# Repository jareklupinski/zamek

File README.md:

# Zamek
Your Digital Keychain.

I want to design the digital equivalent to the analog keychain. It keeps your passwords for you in an easy-to-use and portable, reliable design. It can be used completely standalone, but also with a Desktop App for easier data input.

Prototypes:

[Youtube Function Demo](https://www.youtube.com/watch?v=8wrW3907pkc)

Front View:

Back View:

This project is a Work-In-Progress; all contributions are welcome!

Project Layout:
* brd+sch contains hardware schematic
* desktop-app contains the desktop app
* zamek-src contains arduino source code

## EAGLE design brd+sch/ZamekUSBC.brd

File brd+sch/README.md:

Actual Schematic:

Component Layout:

Routed, produced, and smoke tested. Some validation with sensors to be done...

Front View:

Back View:

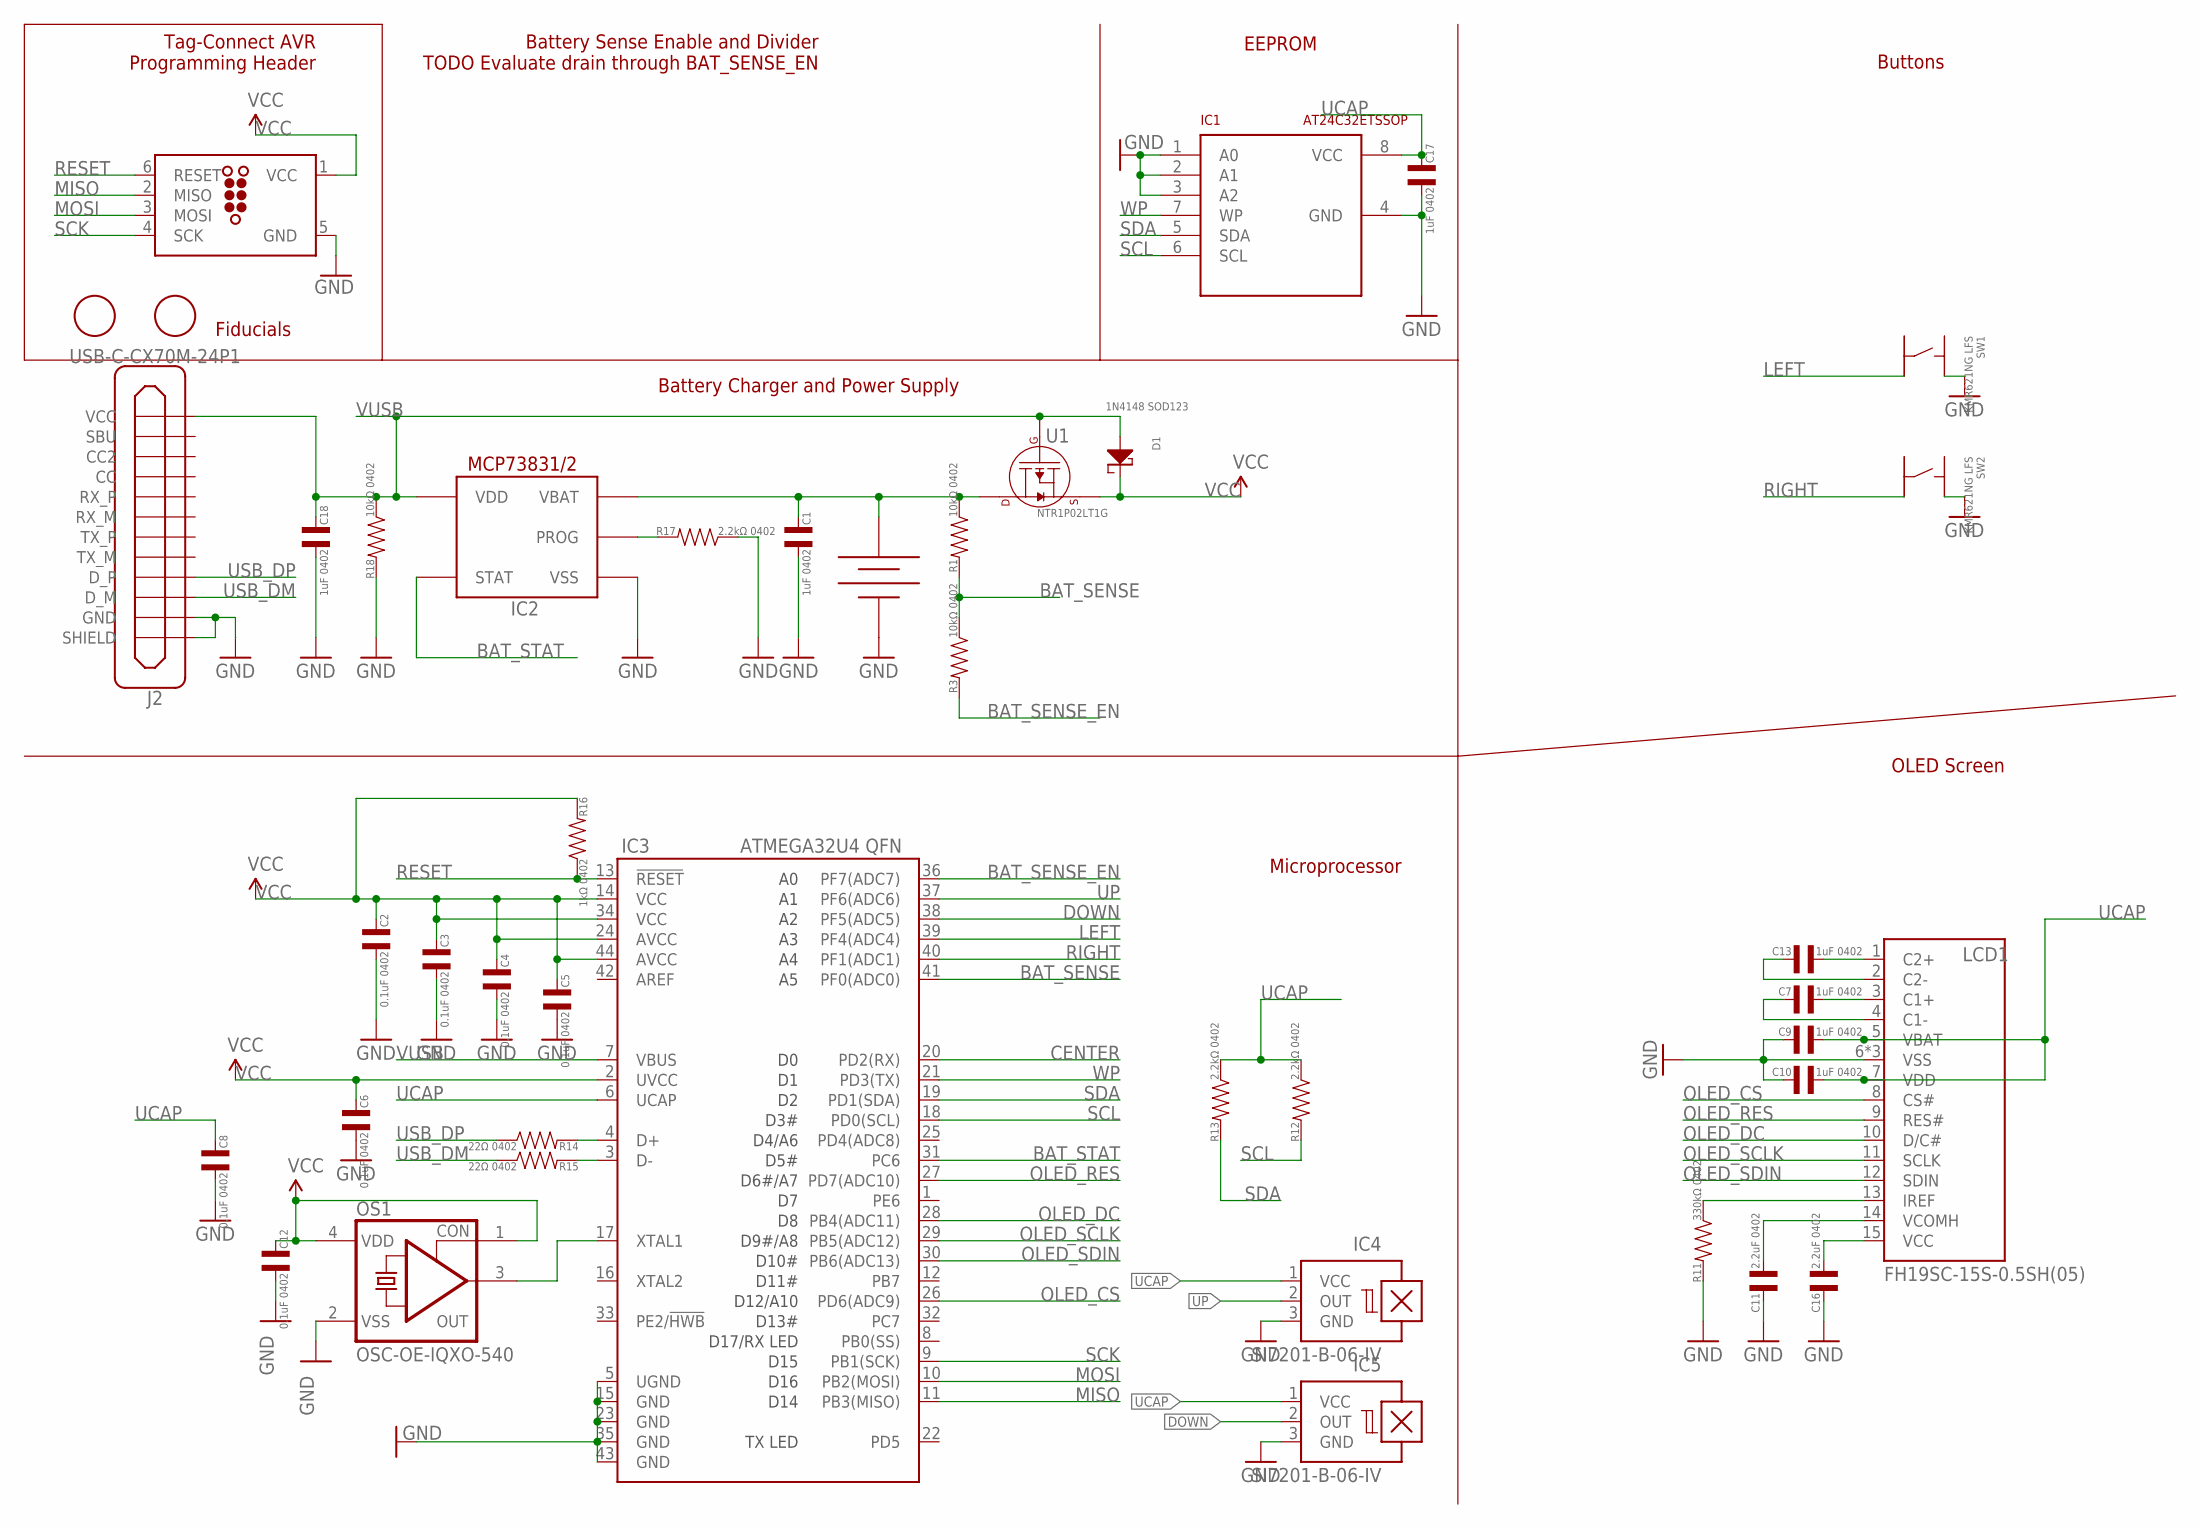
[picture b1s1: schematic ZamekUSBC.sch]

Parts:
BAT1: LIPO201030; 201030LIPO
C1, C7, C9, C10, C13, C17, C18: 1uF 0402; C0402
C2, C3, C4, C5, C6, C8, C12: 0.1uF 0402; C0402
C11, C16: 2.2uF 0402; C0402
D1: 1N4148 SOD123; SOD-123
IC1: AT24C32ETSSOP; TSSOP8-W
IC2: MCP73831; MFSOT23-5L
IC3: ATMEGA32U4 QFN; QFN-44-NOPAD
IC4, IC5: SI7201-B-06-IV; SOT23-W
J1: TC2030-MCP-NLFIX; TC2030-MCP-NL
J2: USB-C-CX70M-24P1; CX70M-24P1
LCD1: FH19SC-15S-0.5SH(05); ER-OLED0.91-3WWFH19C
OS1: OSC-OE-IQXO-540; 2.0X1.6-4-PAD
Q1, Q2: FIDUCIAL; FIDUCIAL_1MM
R1, R3, R18: 10kΩ 0402; R0402
R11: 330kΩ 0402; R0402
R12, R13, R17: 2.2kΩ 0402; R0402
R14, R15: 22Ω 0402; R0402
R16: 1kΩ 0402; R0402
SW1, SW2: KMR621NG LFS; TACT4.2MM
U1: NTR1P02LT1G; SOT-23-3

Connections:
BAT_SENSE: IC3.41 (PF0(ADC0)), R1.P$2, R3.P$1
BAT_SENSE_EN: IC3.36 (PF7(ADC7)), R3.P$2
BAT_STAT: IC2.P$1 (STAT), IC3.31 (PC6)
CENTER: IC3.20 (PD2(RX))
DOWN: IC3.38 (PF5(ADC5)), IC5.2 (OUT)
GND: BAT1.NEG, C1.P$1, C2.P$1, C3.P$1, C4.P$1, C5.P$1, C6.P$1, C8.P$1, C9.P$2, C10.P$2, C11.P$2, C12.P$1, C16.P$2, C17.P$1, C18.P$1, IC1.1 (A0), IC1.2 (A1), IC1.3 (A2), IC1.4 (GND), IC2.P$2 (VSS), IC3.5 (UGND), IC3.15 (GND), IC3.23 (GND), IC3.35 (GND), IC3.43 (GND), IC4.3 (GND), IC5.3 (GND), J1.5 (GND), J2.A1 (GND), J2.A12 (GND), J2.B1 (GND), J2.B12 (GND), J2.SHIELD@1 (SHIELD), J2.SHIELD@2 (SHIELD), J2.SHIELD@3 (SHIELD), J2.SHIELD@4 (SHIELD), LCD1.6 (VSS), LCD1.EP1 (VSS), LCD1.EP2 (VSS), OS1.2 (VSS), R11.P$2, R17.P$1, R18.P$2, SW1.P$2, SW2.P$2
LEFT: IC3.39 (PF4(ADC4)), SW1.P$4
MISO: IC3.11 (PB3(MISO)), J1.2 (MISO)
MOSI: IC3.10 (PB2(MOSI)), J1.3 (MOSI)
unnamed: C13.P$2, LCD1.2 (C2-)
unnamed: C7.P$1, LCD1.3 (C1+)
unnamed: C7.P$2, LCD1.4 (C1-)
unnamed: C13.P$1, LCD1.1 (C2+)
unnamed: IC2.P$5 (PROG), R17.P$2
unnamed: IC3.4 (D+), R14.P$2
unnamed: IC3.17 (XTAL1), OS1.3 (OUT)
unnamed: LCD1.13 (IREF), R11.P$1
unnamed: C11.P$1, LCD1.14 (VCOMH)
unnamed: IC3.3 (D-), R15.P$2
unnamed: C16.P$1, LCD1.15 (VCC)
OLED_CS: IC3.26 (PD6(ADC9)), LCD1.8 (CS#)
OLED_DC: IC3.28 (PB4(ADC11)), LCD1.10 (D/C#)
OLED_RES: IC3.27 (PD7(ADC10)), LCD1.9 (RES#)
OLED_SCLK: IC3.29 (PB5(ADC12)), LCD1.11 (SCLK)
OLED_SDIN: IC3.30 (PB6(ADC13)), LCD1.12 (SDIN)
RESET: IC3.13 (!RESET), J1.6 (RESET), R16.P$1
RIGHT: IC3.40 (PF1(ADC1)), SW2.P$4
SCK: IC3.9 (PB1(SCK)), J1.4 (SCK)
SCL: IC1.6 (SCL), IC3.18 (PD0(SCL)), R12.P$2
SDA: IC1.5 (SDA), IC3.19 (PD1(SDA)), R13.P$2
UCAP: C8.P$2, C9.P$1, C10.P$1, C17.P$2, IC1.8 (VCC), IC3.6 (UCAP), IC4.1 (VCC), IC5.1 (VCC), LCD1.5 (VBAT), LCD1.7 (VDD), R12.P$1, R13.P$1
UP: IC3.37 (PF6(ADC6)), IC4.2 (OUT)
USB_DM: J2.A7 (D_M), J2.B7 (D_M), R15.P$1
USB_DP: J2.A6 (D_P), J2.B6 (D_P), R14.P$1
VBAT: BAT1.POS, C1.P$2, IC2.P$3 (VBAT), R1.P$1, U1.P$3 (DRAIN)
VCC: C2.P$2, C3.P$2, C4.P$2, C5.P$2, C6.P$2, C12.P$2, D1.CATHODE, IC3.2 (UVCC), IC3.14 (VCC), IC3.24 (AVCC), IC3.34 (VCC), IC3.44 (AVCC), J1.1 (VCC), OS1.1 (CON), OS1.4 (VDD), R16.P$2, U1.P$2 (SOURCE)
VUSB: C18.P$2, D1.ANODE, IC2.P$4 (VDD), IC3.7 (VBUS), J2.A4 (VCC), J2.A9 (VCC), J2.B4 (VCC), J2.B9 (VCC), R18.P$1, U1.P$1 (GATE)
WP: IC1.7 (WP), IC3.21 (PD3(TX))

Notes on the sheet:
Tag-Connect AVR Programming Header
Battery Charger and Power Supply
Microprocessor
Battery Sense Enable and Divider TODO Evaluate drain through BAT_SENSE_EN
OLED Screen
Buttons
EEPROM
Fiducials

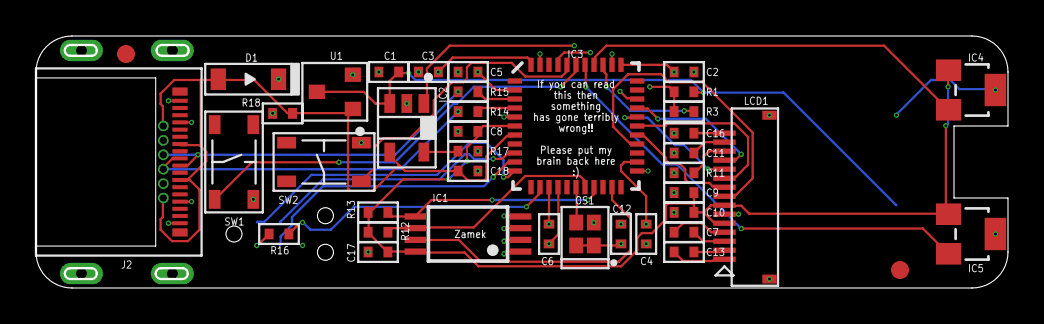
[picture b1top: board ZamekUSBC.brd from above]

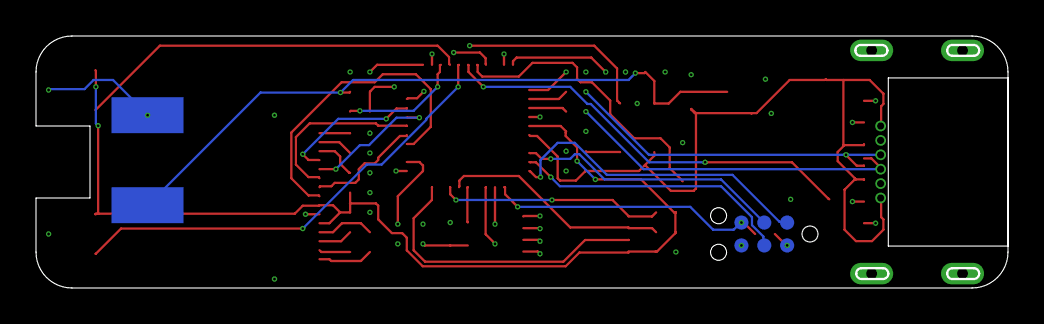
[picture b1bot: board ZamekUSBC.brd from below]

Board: 4 copper layers, 53.9 x 13.9 mm, 42 parts (2 on the bottom side), 37 nets.

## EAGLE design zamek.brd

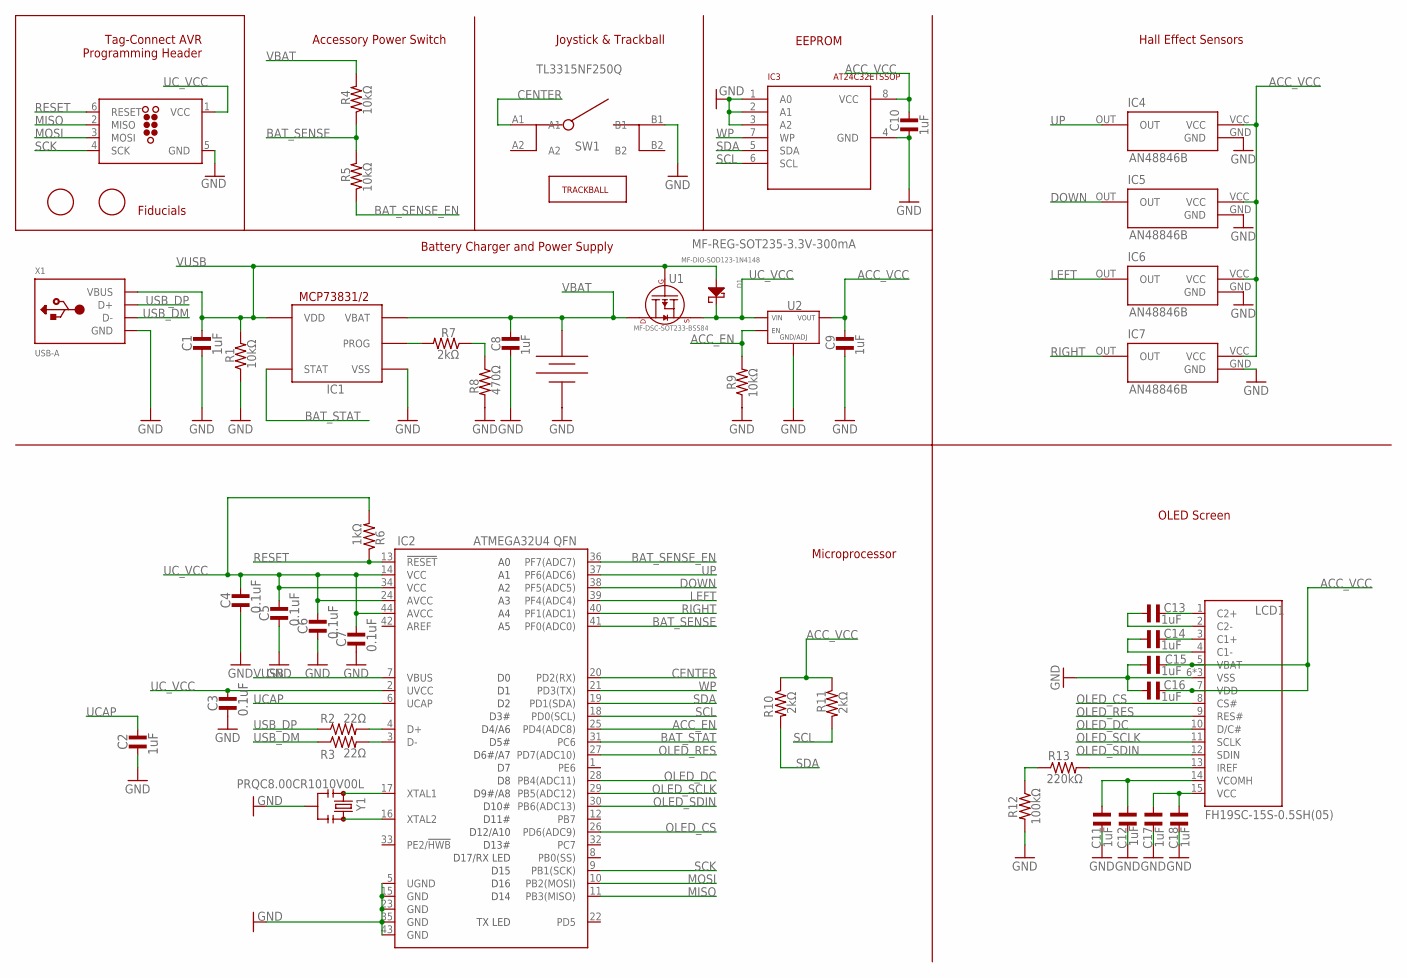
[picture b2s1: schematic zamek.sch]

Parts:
BAT1: LIPO201030; 201030LIPO
C1, C2, C8, C9, C10, C11, C12, C13, C14, C15, C16, C17, C18: 1uF; C0402
C3, C4, C5, C6, C7: 0.1uF; C0402
D1: MF-DIO-SOD123-1N4148; SOD-123
IC1: MCP73831; MFSOT23-5L
IC2: ATMEGA32U4 QFN; QFN-44-NOPAD
IC3: AT24C32ETSSOP; TSSOP8-W
IC4, IC5, IC6, IC7: AN48846B; HALLSENSOR
J1: TC2030-MCP-NLFIX; TC2030-MCP-NL
LCD1: FH19SC-15S-0.5SH(05); ER-OLED0.91-3WWFH19C
R1, R4, R5, R9: 10kΩ; R0402
R2, R3: 22Ω; R0402
R6: 1kΩ; R0402
R7, R10, R11: 2kΩ; R0402
R8: 470Ω; R0402
R12: 100kΩ; R0402
R13: 220kΩ; R0402
SW1: TL3315NF250Q; TRACKBALLBUTTON
SW2: TRACKBALLMECH; TRACKBALL
U1: MF-DSC-SOT233-BSS84; SOT-23-3
U2: MF-REG-SOT235-3.3V-300mA; SOT-23-5
U$1, U$2: FIDUCIAL; FIDUCIAL_1MM
X1: USB-A; MOLEX_480371000
Y1: PRQC8.00CR1010V00L; RESONATOR-SMD

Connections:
ACC_EN: IC2.25 (PD4(ADC8)), R9.P$2, U2.P$3 (EN)
ACC_VCC: C9.P$1, C10.P$1, C15.P$2, C16.P$1, IC3.8 (VCC), IC4.VCC, IC5.VCC, IC6.VCC, IC7.VCC, LCD1.5 (VBAT), LCD1.7 (VDD), R10.P$1, R11.P$1, U2.P$5 (VOUT)
BAT_SENSE: IC2.41 (PF0(ADC0)), R4.P$1, R5.P$2
BAT_SENSE_EN: IC2.36 (PF7(ADC7)), R5.P$1
BAT_STAT: IC1.P$1 (STAT), IC2.31 (PC6)
CENTER: IC2.20 (PD2(RX)), SW1.A1
DOWN: IC2.38 (PF5(ADC5)), IC5.OUT
GND: BAT1.NEG, C1.P$2, C2.P$2, C3.P$2, C4.P$2, C5.P$2, C6.P$2, C7.P$2, C8.P$2, C9.P$2, C10.P$2, C11.P$2, C12.P$2, C15.P$1, C16.P$2, C17.P$2, C18.P$2, IC1.P$2 (VSS), IC2.5 (UGND), IC2.15 (GND), IC2.23 (GND), IC2.35 (GND), IC2.43 (GND), IC3.1 (A0), IC3.2 (A1), IC3.3 (A2), IC3.4 (GND), IC4.GND, IC5.GND, IC6.GND, IC7.GND, J1.5 (GND), LCD1.6 (VSS), LCD1.EP1 (VSS), LCD1.EP2 (VSS), R1.P$1, R8.P$2, R9.P$1, R12.P$2, SW1.B1, U2.P$2 (GND/ADJ), U2.P$4 (GND/ADJ), X1.4 (GND), Y1.2
LEFT: IC2.39 (PF4(ADC4)), IC6.OUT
MISO: IC2.11 (PB3(MISO)), J1.2 (MISO)
MOSI: IC2.10 (PB2(MOSI)), J1.3 (MOSI)
unnamed: C13.P$1, LCD1.2 (C2-)
unnamed: C14.P$2, LCD1.3 (C1+)
unnamed: C14.P$1, LCD1.4 (C1-)
unnamed: C13.P$2, LCD1.1 (C2+)
unnamed: IC1.P$5 (PROG), R7.P$2
unnamed: R12.P$1, R13.P$1
unnamed: IC2.16 (XTAL2), Y1.3
unnamed: LCD1.13 (IREF), R13.P$2
unnamed: C11.P$1, C12.P$1, LCD1.14 (VCOMH)
unnamed: IC2.4 (D+), R2.P$2
unnamed: IC2.3 (D-), R3.P$2
unnamed: IC2.17 (XTAL1), Y1.1
unnamed: R7.P$1, R8.P$1
unnamed: C17.P$1, C18.P$1, LCD1.15 (VCC)
OLED_CS: IC2.26 (PD6(ADC9)), LCD1.8 (CS#)
OLED_DC: IC2.28 (PB4(ADC11)), LCD1.10 (D/C#)
OLED_RES: IC2.27 (PD7(ADC10)), LCD1.9 (RES#)
OLED_SCLK: IC2.29 (PB5(ADC12)), LCD1.11 (SCLK)
OLED_SDIN: IC2.30 (PB6(ADC13)), LCD1.12 (SDIN)
RESET: IC2.13 (!RESET), J1.6 (RESET), R6.P$1
RIGHT: IC2.40 (PF1(ADC1)), IC7.OUT
SCK: IC2.9 (PB1(SCK)), J1.4 (SCK)
SCL: IC2.18 (PD0(SCL)), IC3.6 (SCL), R11.P$2
SDA: IC2.19 (PD1(SDA)), IC3.5 (SDA), R10.P$2
UCAP: C2.P$1, IC2.6 (UCAP)
UC_VCC: C3.P$1, C4.P$1, C5.P$1, C6.P$1, C7.P$1, D1.CATHODE, IC2.2 (UVCC), IC2.14 (VCC), IC2.24 (AVCC), IC2.34 (VCC), IC2.44 (AVCC), J1.1 (VCC), R6.P$2, U1.P$2 (SOURCE), U2.P$1 (VIN)
UP: IC2.37 (PF6(ADC6)), IC4.OUT
USB_DM: R3.P$1, X1.2 (D-)
USB_DP: R2.P$1, X1.3 (D+)
VBAT: BAT1.POS, C8.P$1, IC1.P$3 (VBAT), R4.P$2, U1.P$3 (DRAIN)
VUSB: C1.P$1, D1.ANODE, IC1.P$4 (VDD), IC2.7 (VBUS), R1.P$2, U1.P$1 (GATE), X1.1 (VBUS)
WP: IC2.21 (PD3(TX)), IC3.7 (WP)

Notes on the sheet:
Tag-Connect AVR Programming Header
Battery Charger and Power Supply
Microprocessor
Joystick & Trackball
Accessory Power Switch
OLED Screen
Hall Effect Sensors
EEPROM
Fiducials

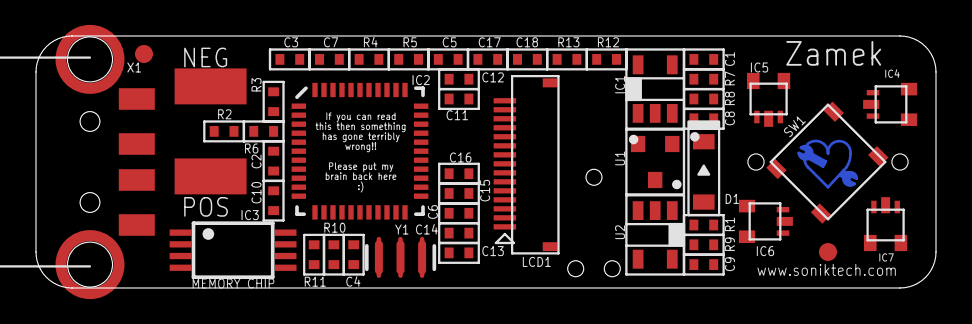
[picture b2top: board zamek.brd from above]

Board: 4 copper layers, 50.0 x 14.0 mm, 50 parts (1 on the bottom side), 43 nets.

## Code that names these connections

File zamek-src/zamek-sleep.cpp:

 #include "zamek-sleep.h"

GLOBAL_VARIABLES

void ZamekSleep::start() {               //enter Sleep Mode
  for ( int i = 0; i < 16; i++ ) pinArray[ i ] = 0;
  pinArrayIndex = 0;
  zamekDisplay.wipeScreen();
  zamekDisplay.drawBitmap( 48, 0, lock, 32, 32, WHITE );
  zamekDisplay.display();
  while ( !digitalRead( BUTTON_CENTER_PIN ));
  zamekDisplay.ssd1306_command( SSD1306_DISPLAYOFF );
  
  pinMode( BUTTON_UP_PIN     , INPUT_PULLUP );
  pinMode( BUTTON_DOWN_PIN   , INPUT_PULLUP );
  pinMode( BUTTON_LEFT_PIN   , INPUT_PULLUP );
  pinMode( BUTTON_RIGHT_PIN  , INPUT_PULLUP );
  pinMode( BAT_SENSE_PIN     , INPUT );
  pinMode( BAT_SENSE_EN_PIN  , INPUT );
  pinMode( BAT_STAT_PIN      , INPUT );
  pinMode( EEPROM_WP_PIN     , INPUT );
  // pinMode( ACC_EN_PIN        , INPUT );
  pinMode( OLED_MOSI_PIN     , INPUT );
  pinMode( OLED_CLK_PIN      , INPUT );
  pinMode( OLED_DC_PIN       , INPUT );
  pinMode( OLED_RESET_PIN    , INPUT );
  pinMode( OLED_CS_PIN       , INPUT );

  set_sleep_mode( SLEEP_MODE_PWR_DOWN ); // Set CPU Sleep Mode
  analogReference( DEFAULT ); // Power down internal reference
  PLLCSR &= ~( 1 << PLLE );   // Disable the USB Clock (PPL)
  USBCON &= ~( 1 << USBE );   // Disable the USB
  UDINT  &= ~( 1 << SUSPI );  // UDINT.SUSPI = 0; Usb_ack_suspend
  USBCON |=  ( 1 << FRZCLK ); // USBCON.FRZCLK = 1; Usb_freeze_clock
  ADCSRA = 0b00000000;        // Disable ADC
  power_adc_disable();
  wdt_disable();  
  sleep_enable();
  sleep_mode();
  //Current Sleep Power Consumption: 240uA
  //Atmega32u4 datasheet claims it can go as low as 15uA
  //Power Regulator's Iq is 65uA
  //TODO Evaluate other potential sources of current leaks
  //TODO Evaluate 'cleaner' methods for coming out of sleep and resetting
  sleep_disable();
  asm volatile ( "  jmp 0" );
}

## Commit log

2018-07-05 design tested: working
2019-01-28 restructured the project, so that it will be easier for others to use.
2019-01-28 updated docu a bit now everything is nicely structured.
2019-01-28 added a description for the brd and sch files.
2020-07-19 add usbc variant

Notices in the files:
parts and their libraries:
SparkFun-DigitalIC: Licensing: CC v3.0 Share-Alike You are welcome to use this library for commercial purposes.
sonik: ©2009 ROFA.cz - modified and updated by Robert Darlington ‹rdarlington@gmail.com›
